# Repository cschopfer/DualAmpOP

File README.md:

# DualAmpOP

[cschopfer/DualAmpOP](https://github.com/cschopfer/DualAmpOP)

Un petit PCB pour avoir un ampli-op double disponible pour vos bricolages sur breadboard.

**Statut :** prototype v2.0 monté et testé, fonctionne très bien.
Cette v2.0 remplace une v1 qui n'a jamais été produite.

## Le principe

Le PCB accepte tout double ampli-op compatible broche à broche en boîtier
SOIC-8 — LM358, MCP6002, etc.

Chaque étage dispose d'un réseau de résistances (R1 à R8 pour le premier
étage, R9 à R17 pour le second, sur le même principe) qu'il suffit de
câbler pour obtenir la topologie voulue :

- **n.m.** — ne rien monter
- **0 Ω** — un pont (connexion directe)
- **valeur** — une vraie résistance, pour régler un gain ou une fréquence de coupure

## Configurations

| Montage | R1 | R2 | R3 | R4 | R5 | R6 | R7 | R8 | Gain / formule |
|---|---|---|---|---|---|---|---|---|---|
| Inverseur | valeur | n.m. | valeur | n.m. | 0 Ω | n.m. | n.m. | n.m. | `Vout = −Vin·(R3/R1)` |
| Non-inverseur | n.m. | 0 Ω | valeur | n.m. | n.m. | n.m. | valeur | 0 Ω | `Vout = Vin·(1 + R3/R7)` |
| Transimpédance | 0 Ω | n.m. | Rf | n.m. | 0 Ω | n.m. | n.m. | n.m. | `Vout = −Iin·R3` |
| Suiveur | n.m. | 0 Ω | 0 Ω | n.m. | n.m. | n.m. | n.m. | 0 Ω | `Vout = Vin` |
| Passe-bas actif (intégrateur) | R | n.m. | C* | n.m. | n.m. | n.m. | n.m. | n.m. | `fc = 1/(2πRC)` |
| Passe-haut actif | — | — | — | — | — | — | — | — | à venir |
| Sallen-Key | — | — | — | — | — | — | — | — | à venir |

\* Pour les filtres actifs, la résistance concernée est remplacée par un
condensateur céramique 0805 de même taille.

### Alimentation symétrique ou asymétrique

R10 relie le rail V- à la masse.

- **Non montée** : alimentation symétrique (Vcc+ / Vcc-)
- **Montée à 0 Ω** : alimentation asymétrique, entre Vcc et GND

## Arborescence

```
hardware/
  DualAmpOP.kicad_pro
  exports/
    PDF/
    gerbers/
    3D/
docs/
  images/
    IMG_3928.jpeg
```

## Licence

À définir.

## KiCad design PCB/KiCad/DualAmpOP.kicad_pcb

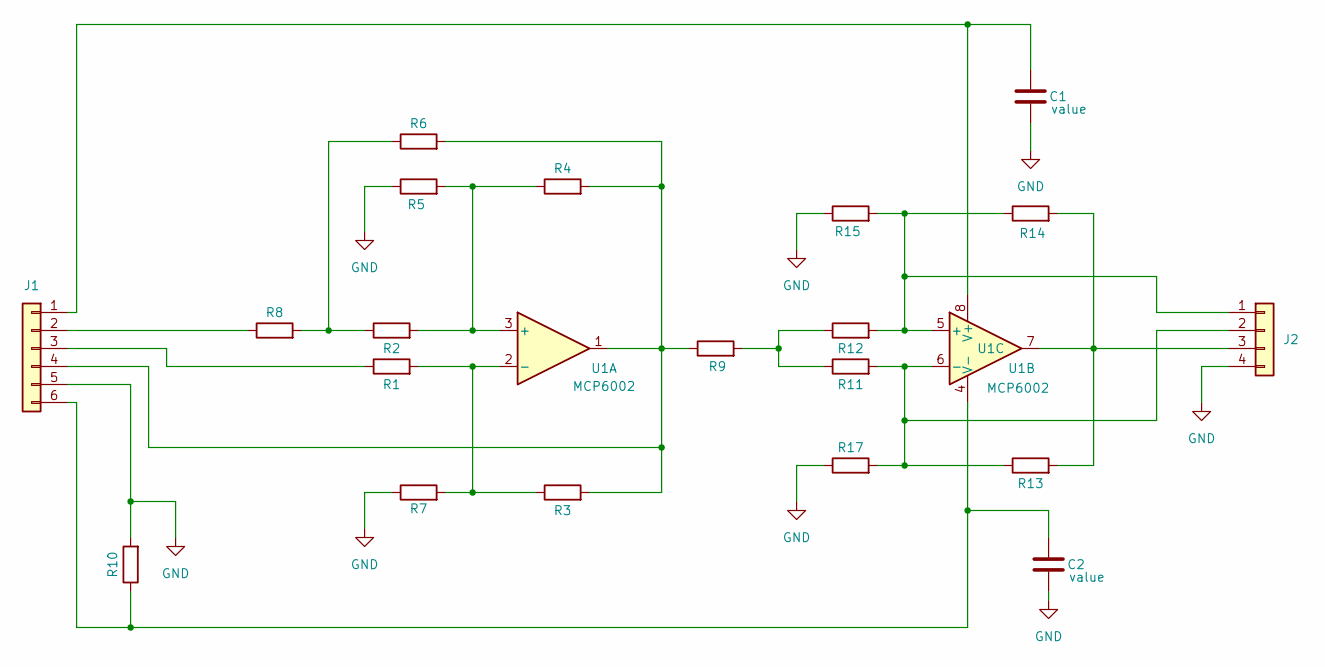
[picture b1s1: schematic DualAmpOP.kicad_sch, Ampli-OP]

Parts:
C1, C2: value; C_0805_2012Metric_Pad1.18x1.45mm_HandSolder
J1: PinHeader_1x06_P2.54mm_Vertical
J2: PinHeader_1x04_P2.54mm_Vertical
R1, R2, R3, R5, R11, R12, R13, R15: R; R_0805_2012Metric_Pad1.20x1.40mm_HandSolder
R4, R6, R7, R8, R9, R10, R14, R17: value; R_0805_2012Metric_Pad1.20x1.40mm_HandSolder
U1: MCP6002; SOIC-8_3.9x4.9mm_P1.27mm

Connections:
GND: C1.2, C2.2, J1.5, J2.4, R5.1, R7.1, R10.2, R15.1, R17.1
unnamed: C1.1, J1.1, U1.8 (V+)
unnamed: J1.2, R8.1
unnamed: J1.3, R1.1
unnamed: J1.4, R3.2, R4.2, R6.2, R9.1, U1.1
unnamed: C2.1, J1.6, R10.1, U1.4 (V-)
unnamed: J2.1, R12.2, R14.1, R15.2, U1.5 (+)
unnamed: J2.2, R11.2, R13.1, R17.2, U1.6 (-)
unnamed: J2.3, R13.2, R14.2, U1.7
unnamed: R2.1, R6.1, R8.2
unnamed: R9.2, R11.1, R12.1
unnamed: R2.2, R4.1, R5.2, U1.3 (+)
unnamed: R1.2, R3.1, R7.2, U1.2 (-)

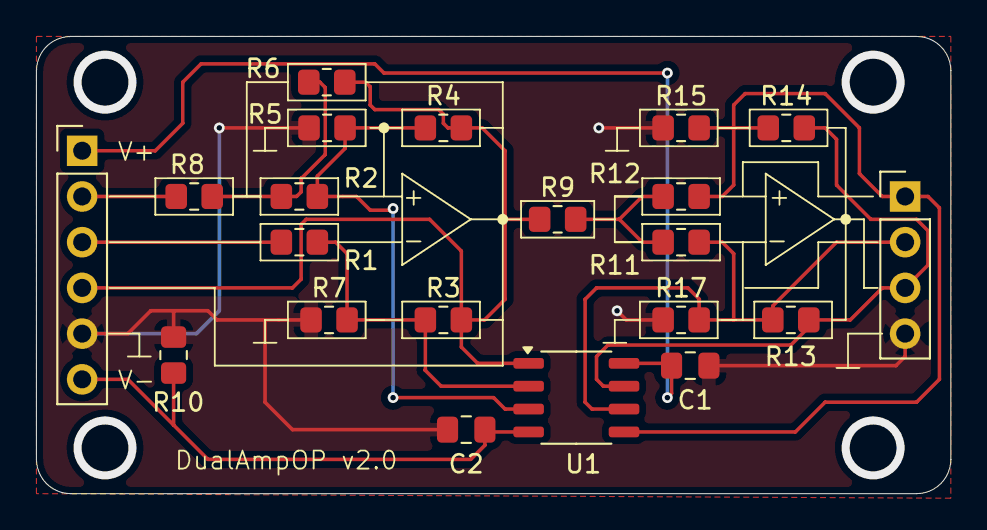
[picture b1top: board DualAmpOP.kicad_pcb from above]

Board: 2 copper layers, 50.8 x 25.4 mm, 21 parts (0 on the bottom side), 13 nets.

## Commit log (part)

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2026-01-04 Premier commit v1
2026-05-14 Finalisation V1 + renommage projet
2026-05-14 Nouvelle version 2 plus pratique
2026-05-14 Modification R6 pour filtre Sallen-key
